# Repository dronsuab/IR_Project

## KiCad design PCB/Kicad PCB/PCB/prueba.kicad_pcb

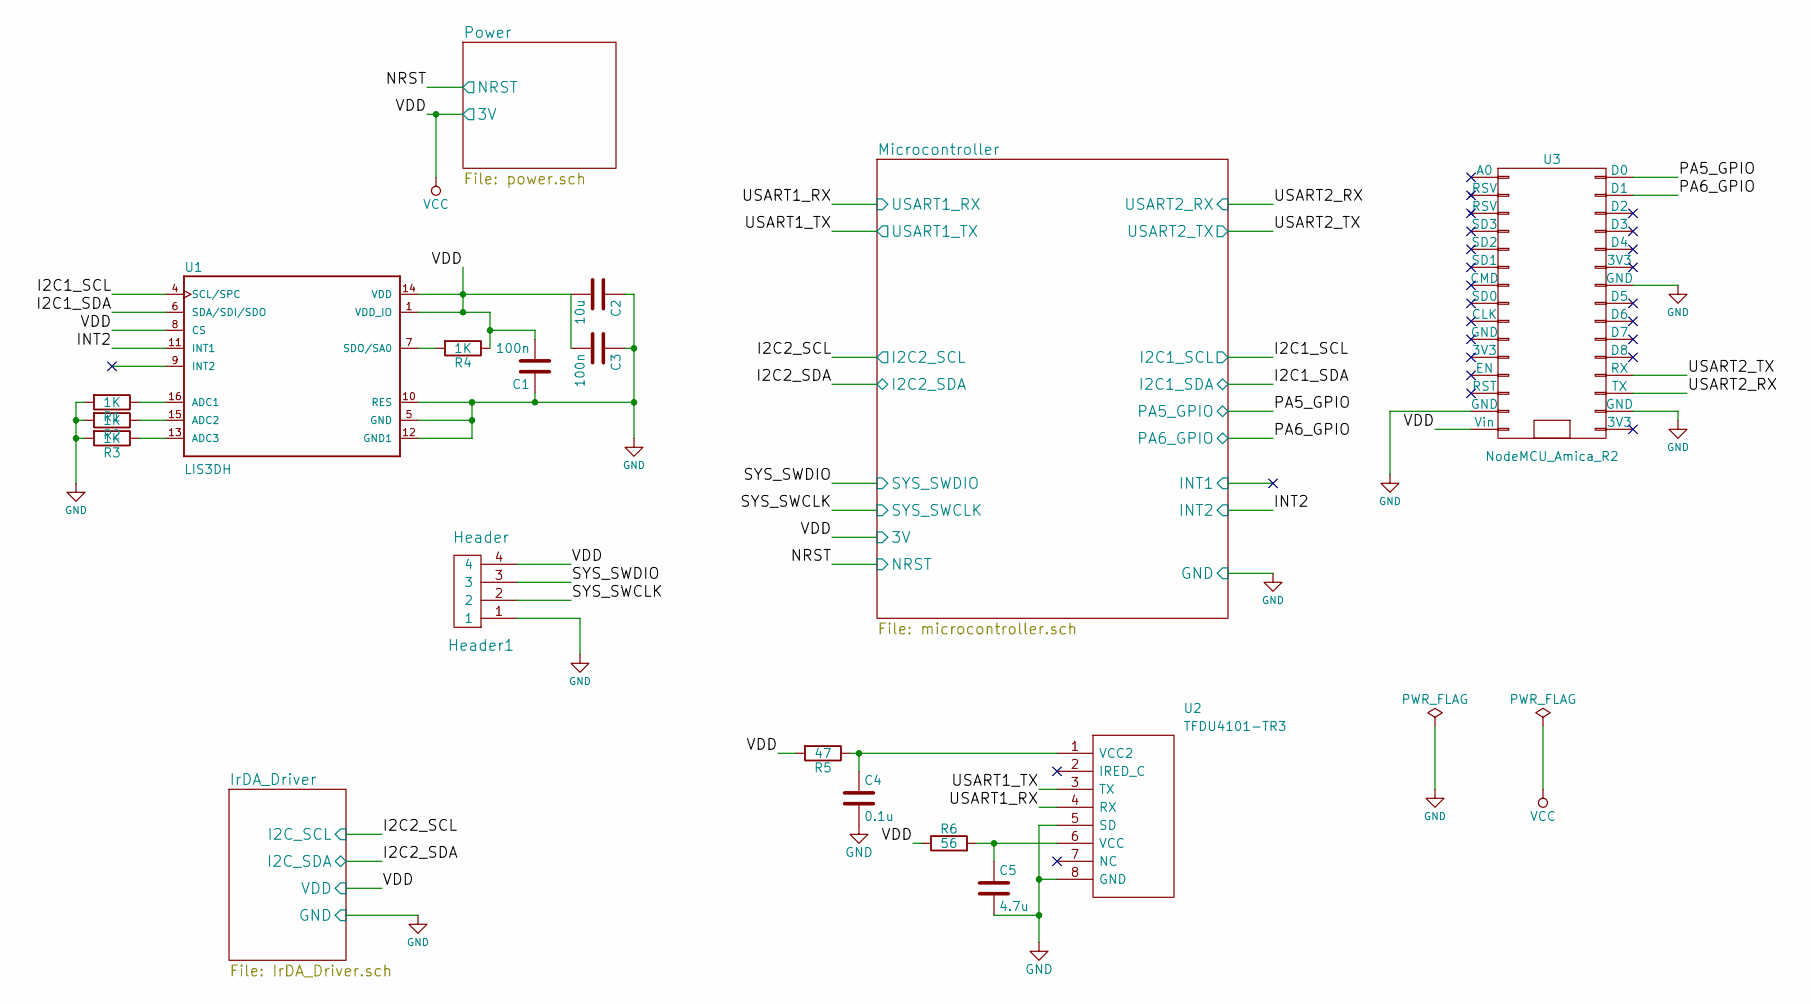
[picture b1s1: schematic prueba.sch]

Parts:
C1, C3: 100n; C_0201
C2: 10u; C_0201
C4: 0.1u; C_0201
C5: 4.7u; C_0201
Header1: Header; DIP-4_W7.62mm
R1, R2, R3, R4: 1K; R_0201
R5: 47; R_0201
R6: 56; R_0201
U1: LIS3DH; PQFN50P300X300X100-16N
U2: TFDU4101-TR3; Manufacturer_Part_Number TFDU4101-TR3
U3: NodeMCU_Amica_R2

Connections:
/I2C1_SCL: U1.4 (SCL/SPC); also elsewhere on the board
/I2C1_SDA: U1.6 (SDA/SDI/SDO); also elsewhere on the board
/INT2: U1.11 (INT1); also elsewhere on the board
/PA5_GPIO: U3.30 (D0); also elsewhere on the board
/PA6_GPIO: U3.29 (D1); also elsewhere on the board
/SYS_SWCLK: Header1.2; also elsewhere on the board
/SYS_SWDIO: Header1.3; also elsewhere on the board
/USART1_RX: U2.4 (RX); also elsewhere on the board
/USART1_TX: U2.3 (TX); also elsewhere on the board
/USART2_RX: U3.18 (TX); also elsewhere on the board
/USART2_TX: U3.19 (RX); also elsewhere on the board
GND: C1.1, C2.1, C3.1, C4.2, C5.2, Header1.1, R1.2, R2.2, R3.2, U1.5 (GND), U1.10 (RES), U1.12 (GND1), U2.5 (SD), U2.8 (GND), U3.14 (GND), U3.17 (GND), U3.24 (GND); also elsewhere on the board
unnamed: C4.1, R5.1, U2.1 (VCC2)
unnamed: C5.1, R6.2, U2.6 (VCC)
unnamed: R1.1, U1.16 (ADC1)
unnamed: R2.1, U1.15 (ADC2)
unnamed: R3.1, U1.13 (ADC3)
unnamed: R4.2, U1.7 (SDO/SA0)
VCC: C1.2, C2.2, C3.2, Header1.4, R4.1, R5.2, R6.1, U1.1 (VDD_IO), U1.8 (CS), U1.14 (VDD), U3.15 (Vin); also elsewhere on the board

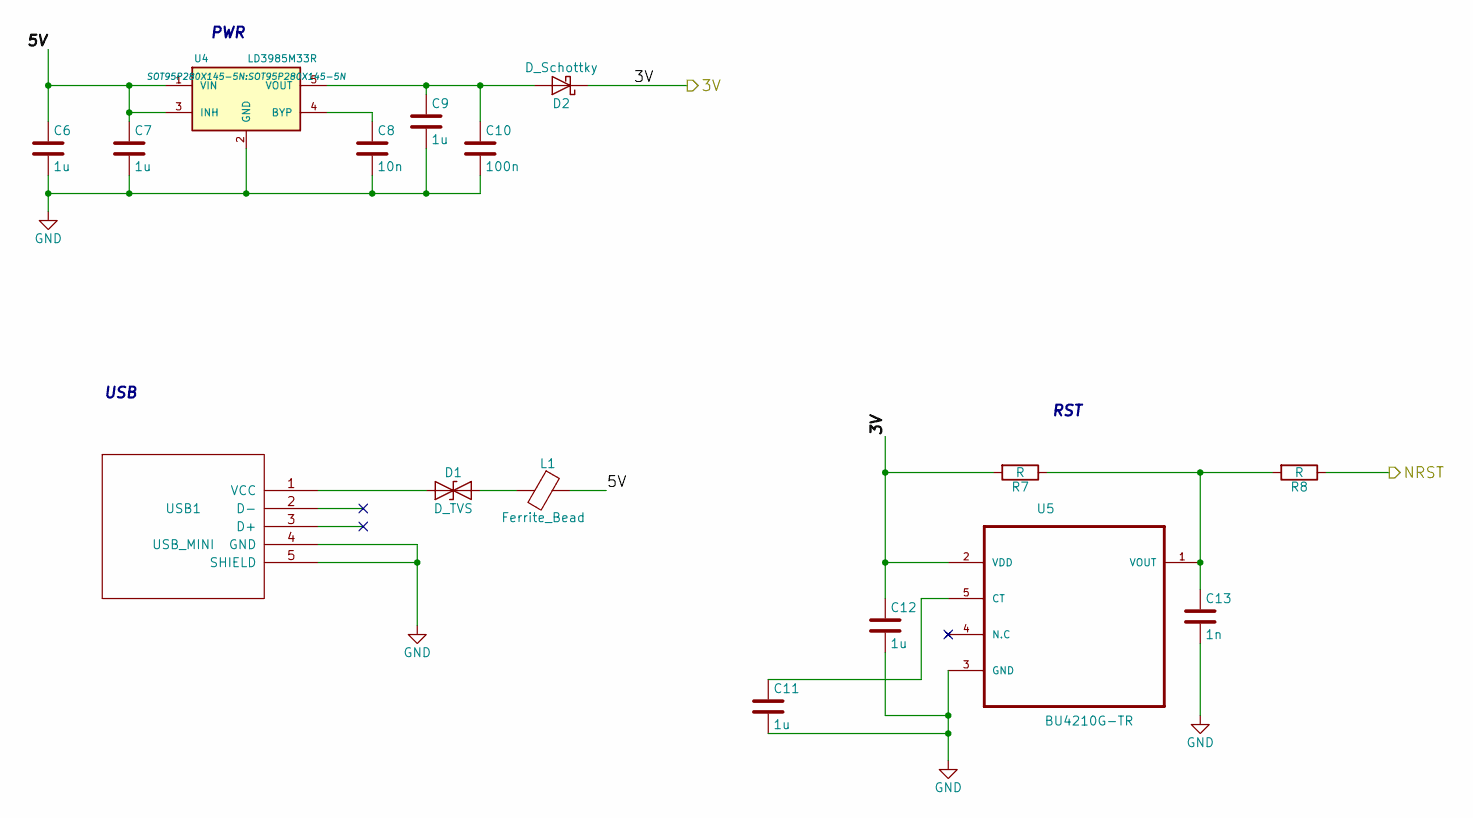
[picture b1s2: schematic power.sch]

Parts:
C6, C7, C9, C11, C12: 1u; C_0201
C8: 10n; C_0201
C10: 100n; C_0201
C13: 1n; C_0201
D1: D_TVS; D_0603
D2: D_Schottky; D_0603
L1: Ferrite_Bead; 0603-NO
R7, R8: R; R_0201
U4: LD3985M33R; SOT95P280X145-5N
U5: BU4210G-TR; SOT95P280X125-5N
USB1: USB_MINI; HRS_ZX62D-B-5P8

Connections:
/NRST: R8.1; also elsewhere on the board
/Power/5V: C6.1, C7.1, L1.1, U4.1 (VIN), U4.3 (INH)
GND: C6.2, C7.2, C8.2, C9.2, C10.2, C11.2, C12.2, C13.2, U4.2 (GND), U5.3 (GND), USB1.4 (GND), USB1.5 (SHIELD); also elsewhere on the board
unnamed: C8.1, U4.4 (BYP)
unnamed: C9.1, C10.1, D2.2 (A), U4.5 (VOUT)
unnamed: C11.1, U5.5 (CT)
unnamed: C13.1, R7.1, R8.2, U5.1 (VOUT)
unnamed: D1.1 (A1), USB1.1 (VCC)
unnamed: D1.2 (A2), L1.2
VCC: C12.1, D2.1 (K), R7.2, U5.2 (VDD); also elsewhere on the board

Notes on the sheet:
PWR
USB
RST

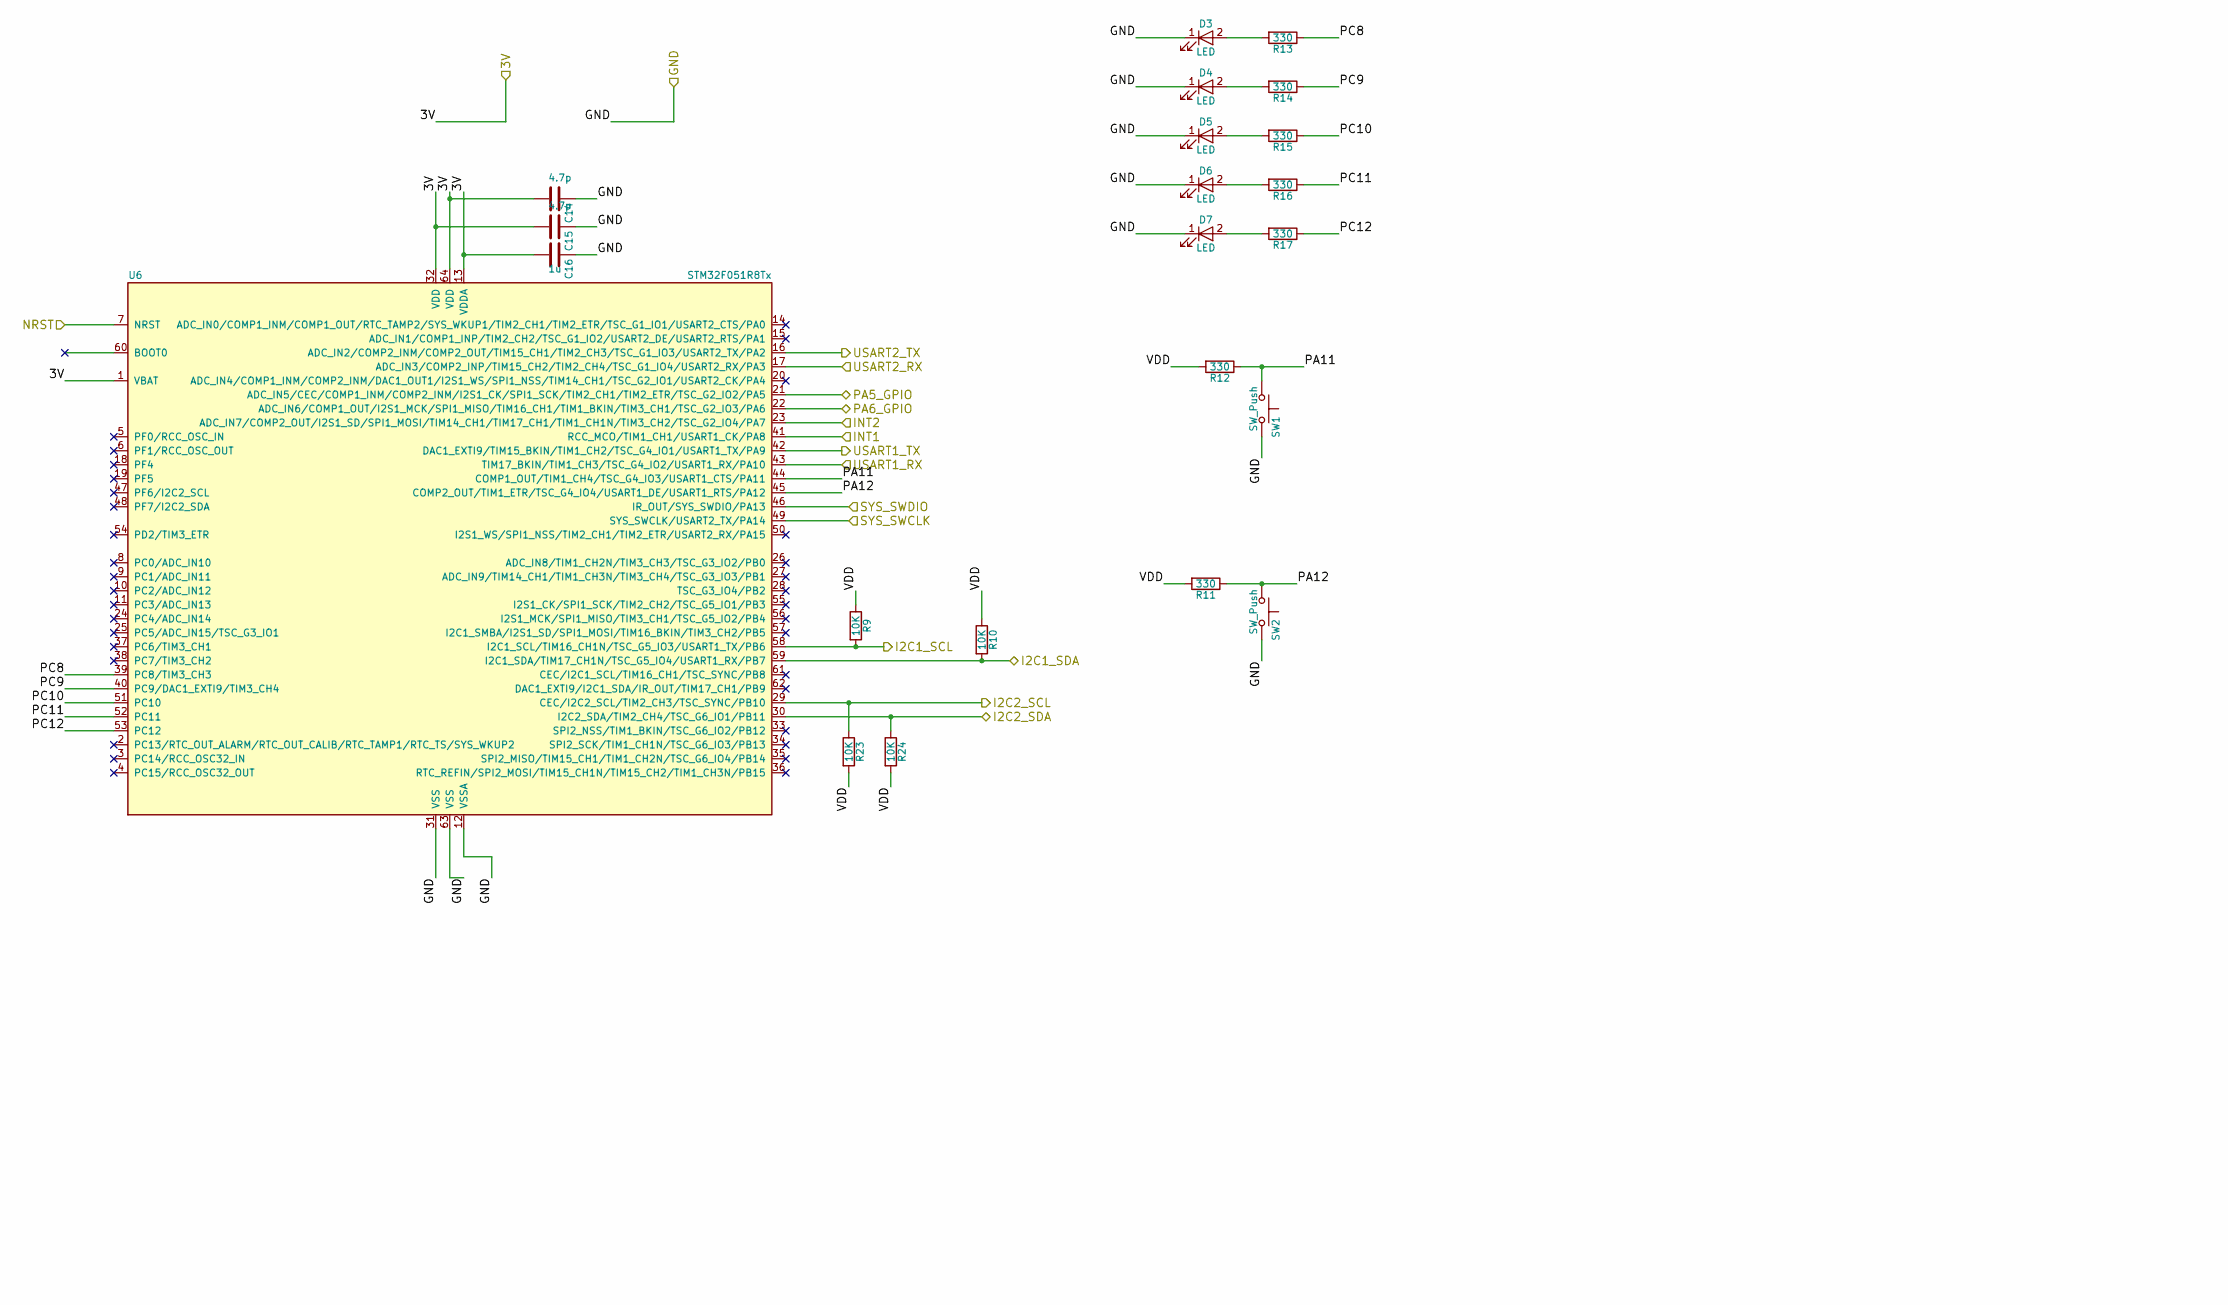
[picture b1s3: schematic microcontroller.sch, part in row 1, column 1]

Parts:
C14, C15: 4.7p; C_0201
C16: 1u; C_0201
D3, D4, D5, D6, D7: LED; LED-L1T2_LUMILEDS
R9, R10, R23, R24: 10K; R_0201
R11, R12, R13, R14, R15, R16, R17: 330; R_0201
SW1, SW2: SW_Push; Nidec_Copal_SH-7010A
U6: STM32F051R8Tx; QFP50P1200X1200X160-64N

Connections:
/I2C1_SCL: R9.2, U6.58 (I2C1_SCL/TIM16_CH1N/TSC_G5_IO3/USART1_T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); also elsewhere on the board
/I2C1_SDA: R10.2, U6.59 (I2C1_SDA/TIM17_CH1N/TSC_G5_IO4/USART1_R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); also elsewhere on the board
/I2C2_SCL: R23.1, U6.29 (CEC/I2C2_SCL/TIM2_CH3/TSC_SYNC/PB10); also elsewhere on the board
/I2C2_SDA: R24.1, U6.30 (I2C2_SDA/TIM2_CH4/TSC_G6_IO1/PB11); also elsewhere on the board
/INT2: U6.23 (ADC_IN7/COMP2_OUT/I2S1_SD/SPI1_MOSI/TIM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); also elsewhere on the board
/Microcontroller/INT1: U6.41 (RCC_MCO/TIM1_CH1/USART1_CK/PA8)
/Microcontroller/PA11: R12.1, SW1.1, U6.44 (COMP1_OUT/TIM1_CH4/TSC_G4_IO3/USART1_CT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)
/Microcontroller/PA12: R11.1, SW2.1, U6.45 (COMP2_OUT/TIM1_ETR/TSC_G4_IO4/USART1_DE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)
/Microcontroller/PC8: R13.1, U6.39 (PC8/TIM3_CH3)
/Microcontroller/PC9: R14.1, U6.40 (PC9/DAC1_EXTI9/TIM3_CH4)
/Microcontroller/PC10: R15.1, U6.51 (PC10)
/Microcontroller/PC11: R16.1, U6.52 (PC11)
/Microcontroller/PC12: R17.1, U6.53 (PC12)
/Microcontroller/VDD: R9.1, R10.1, R11.2, R12.2, R23.2, R24.2
/NRST: U6.7 (NRST); also elsewhere on the board
/PA5_GPIO: U6.21 (ADC_IN5/CEC/COMP1_INM/COMP2_INM/I2S1_CK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); also elsewhere on the board
/PA6_GPIO: U6.22 (ADC_IN6/COMP1_OUT/I2S1_MCK/SPI1_MISO/TI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); also elsewhere on the board
/SYS_SWCLK: U6.49 (SYS_SWCLK/USART2_TX/PA14); also elsewhere on the board
/SYS_SWDIO: U6.46 (IR_OUT/SYS_SWDIO/PA13); also elsewhere on the board
/USART1_RX: U6.43 (TIM17_BKIN/TIM1_CH3/TSC_G4_IO2/USART1_R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); also elsewhere on the board
/USART1_TX: U6.42 (DAC1_EXTI9/TIM15_BKIN/TIM1_CH2/TSC_G4_I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); also elsewhere on the board
/USART2_RX: U6.17 (ADC_IN3/COMP2_INP/TIM15_CH2/TIM2_CH4/TS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); also elsewhere on the board
/USART2_TX: U6.16 (ADC_IN2/COMP2_INM/COMP2_OUT/TIM15_CH1/T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); also elsewhere on the board
GND: C14.1, C15.1, C16.1, D3.1 (K), D4.1 (K), D5.1 (K), D6.1 (K), D7.1 (K), SW1.2, SW2.2, U6.12 (VSSA), U6.31 (VSS), U6.63 (VSS); also elsewhere on the board
unnamed: D3.2 (A), R13.2
unnamed: D4.2 (A), R14.2
unnamed: D5.2 (A), R15.2
unnamed: D6.2 (A), R16.2
unnamed: D7.2 (A), R17.2
VCC: C14.2, C15.2, C16.2, U6.1 (VBAT), U6.13 (VDDA), U6.32 (VDD), U6.64 (VDD); also elsewhere on the board

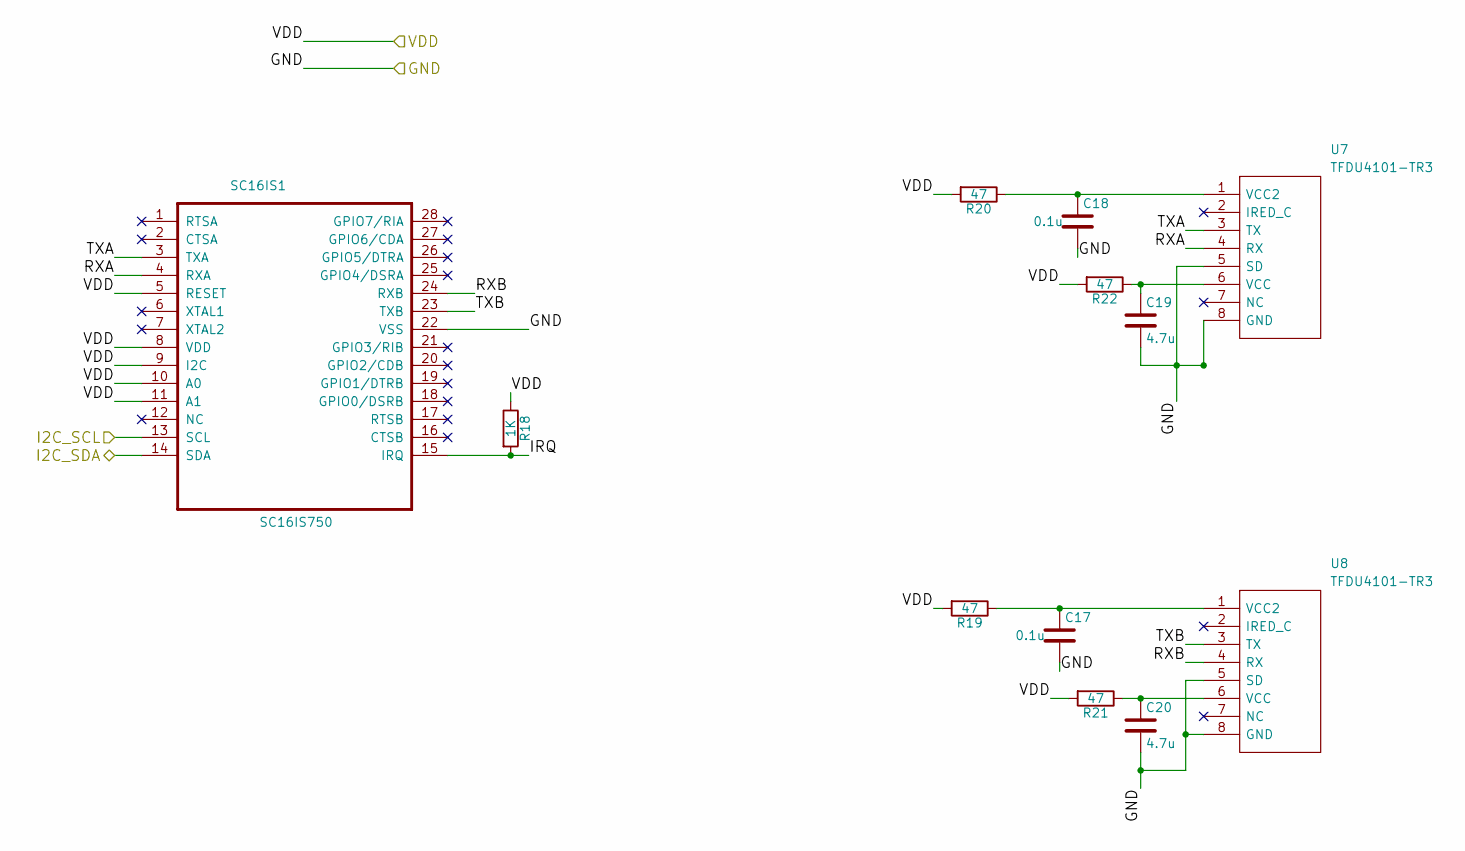
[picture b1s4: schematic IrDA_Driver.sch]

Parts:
C17, C18: 0.1u; C_0201
C19, C20: 4.7u; C_0201
R18: 1K; R_0201
R19, R20, R21, R22: 47; R_0201
SC16IS1: SC16IS750; SOP65P640X110-28N
U7, U8: TFDU4101-TR3; Manufacturer_Part_Number TFDU4101-TR3

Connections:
/I2C2_SCL: SC16IS1.13 (SCL); also elsewhere on the board
/I2C2_SDA: SC16IS1.14 (SDA); also elsewhere on the board
/IrDA_Driver/IRQ: R18.2, SC16IS1.15 (IRQ)
/IrDA_Driver/RXA: SC16IS1.4 (RXA), U7.4 (RX)
/IrDA_Driver/RXB: SC16IS1.24 (RXB), U8.4 (RX)
/IrDA_Driver/TXA: SC16IS1.3 (TXA), U7.3 (TX)
/IrDA_Driver/TXB: SC16IS1.23 (TXB), U8.3 (TX)
GND: C17.2, C18.2, C19.2, C20.2, SC16IS1.22 (VSS), U7.5 (SD), U7.8 (GND), U8.5 (SD), U8.8 (GND); also elsewhere on the board
unnamed: C17.1, R19.1, U8.1 (VCC2)
unnamed: C18.1, R20.1, U7.1 (VCC2)
unnamed: C19.1, R22.1, U7.6 (VCC)
unnamed: C20.1, R21.1, U8.6 (VCC)
VCC: R18.1, R19.2, R20.2, R21.2, R22.2, SC16IS1.5 (RESET), SC16IS1.8 (VDD), SC16IS1.9 (I2C), SC16IS1.10 (A0), SC16IS1.11 (A1); also elsewhere on the board

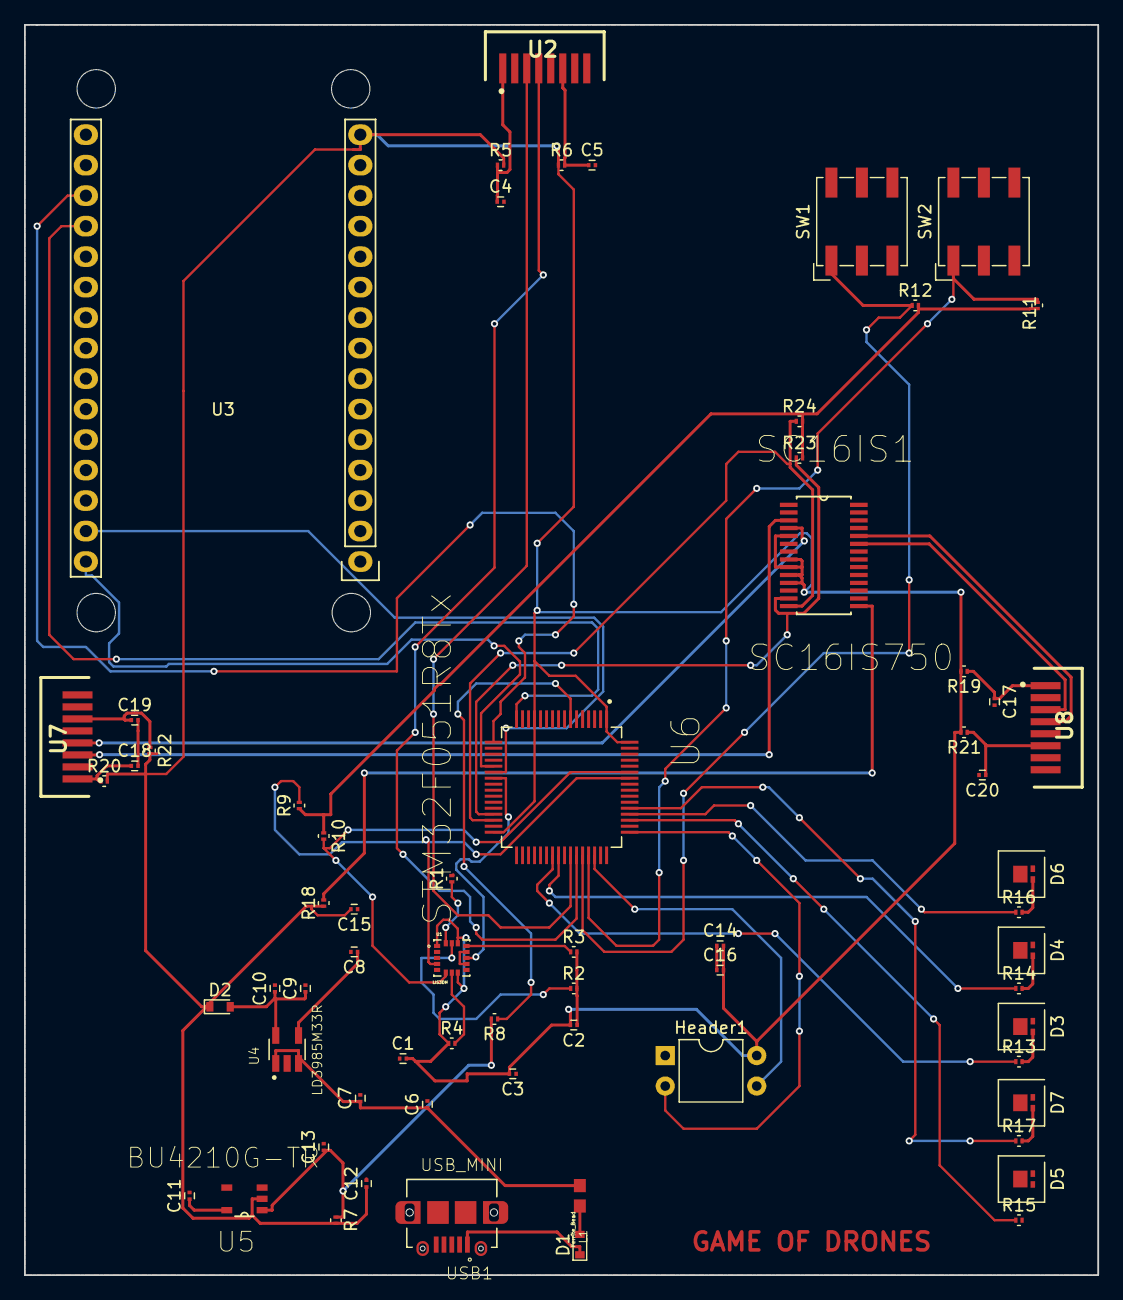
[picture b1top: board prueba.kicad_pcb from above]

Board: 2 copper layers, 89.4 x 104.1 mm, 65 parts (0 on the bottom side), 51 nets.

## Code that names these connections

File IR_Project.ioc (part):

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Mcu.Name=STM32F051R8Tx
Mcu.Package=LQFP64
Mcu.UserName=STM32F051R8Tx
PA0.Mode=IN0
PA0.Signal=ADC_IN0
PA1.Mode=IN1
PA1.Signal=ADC_IN1
PA10.Mode=IrDA
PA10.Signal=USART1_RX
PA2.Mode=Synchronous
PA2.Signal=USART2_TX
PA3.Mode=Synchronous
PA3.Signal=USART2_RX
PA4.Mode=Synchronous
PA4.Signal=USART2_CK
PA5.Mode=Full_Duplex_Master
PA5.Signal=SPI1_SCK
PA6.Mode=Full_Duplex_Master
PA6.Signal=SPI1_MISO
PA7.Mode=Full_Duplex_Master
PA7.Signal=SPI1_MOSI
PA9.Mode=IrDA
PA9.Signal=USART1_TX
PC7.Signal=GPIO_Output
PC8.Signal=GPIO_Output
PC9.Signal=GPIO_Output
board=IR_Project

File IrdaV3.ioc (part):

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Mcu.Name=STM32F051R8Tx
Mcu.Package=LQFP64
Mcu.UserName=STM32F051R8Tx
PA10.Mode=IrDA
PA10.Signal=USART1_RX
PA2.Mode=Synchronous
PA2.Signal=USART2_TX
PA3.Mode=Synchronous
PA3.Signal=USART2_RX
PA4.Mode=Synchronous
PA4.Signal=USART2_CK
PA9.Mode=IrDA
PA9.Signal=USART1_TX
PB6.Mode=I2C
PB6.Signal=I2C1_SCL
PB7.Mode=I2C
PB7.Signal=I2C1_SDA
board=IrdaV3

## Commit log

2017-10-22 UART
    UART for WIFI communication implemented.
2017-10-26 Circular buffer implemented
2017-10-29 Interrupts implemented.
2017-11-18 uart implemented.
2017-11-18 GPIO Toggle modified. GPIO example in main.c
2017-11-18 RTOS EXAMPLE
2017-11-19 uart example in main.c
2017-11-19 CircularBuffer directory updated.
2017-11-25 (Provisional) maybe some files are missing
2018-02-02 RTOS implemented with serial transmission task.
2018-02-02 Irda Test Funcionando
2018-02-11 UART reception implemented.
2018-02-11 Completed code of UART reception.
2018-02-25 BridgeMode implemented according to the protocol.
2018-03-07 Button implemented to simulate a IR shot reception.
2018-03-09 Drone App created to manage the task creation.
2018-03-20 Specs included with information about the project
2018-03-21 Structures modified to follow a standard.
2018-03-28 IrDA implemented (not tested), Irda Transceiver and RFID nucleo specs included.
2018-03-28 IrDA modified.
2018-04-20 New branch created for IrDA tests.
2018-04-25 Semaphores implemented to guarantee communication between tasks.
2018-05-13 IrDA implemented successfully.
2018-05-17 Middleware update to implement a bridge mode with semaphores.
2018-05-23 BridgeMode updated.
2018-05-25 Specs updated.
2018-05-25 Kicad parts folder created with the Vishay TFDU4101 transceiver.
2018-05-28 Device and TFD4101 libraries updated
2018-06-02 PCB created.
2018-06-04 SC16IS752IPW symbol implemented.
2018-06-12 SC16i52 connected with 2 transceivers.
2018-06-12 SC16IS752 datasheet
2018-06-17 PCB updated to follow the ECM rules.
2018-06-18 Netlist finished.
2018-06-18 PCBnet updated.
2018-06-18 PCB schematic updated.
2018-06-22 PCB updated with partial routing
2018-06-27 PCB design updated
2018-06-29 PCB finished, without ground and vcc plane
2018-07-02 Final code
2018-07-02 Ground Plane added.
